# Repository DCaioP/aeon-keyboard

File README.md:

# Documentação do Sistema

## Sumário
- [Dados do Cliente](#dados-do-cliente)
- [Equipe de Desenvolvimento](#equipe-de-desenvolvimento)
- [Introdução](#introdução)
- [Objetivo](#objetivo)
- [Escopo](#escopo)
- [Backlogs do Produto](#backlogs-do-produto)
- [Cronograma](#cronograma)
- [Materiais e Métodos](#materiais-e-métodos)
- [Resultados](#resultados)
- [Conclusão](#conclusão)
- [Homologação do MVP junto ao Cliente](#homologação-do-mvp-junto-ao-cliente)
- [Divulgação](#divulgação)
- [Carta de Apresentação](#carta-de-apresentação)
- [Carta de Autorização](#carta-de-autorização)
- [Relato Individual do Processo](#relato-individual-do-processo)

---

## Dados do Cliente

- **Título do Projeto**: aeon: Teclado Ergonômico Split Ortolinear
- **Cliente**: BrainX
- **CNPJ/CPF**: 58.450.889/0001-99
- **Contato**: Caio Pontes Magalhães
- **Email do contato**: caio@brainx.dev

---

## Equipe de Desenvolvimento

| Nome completo        | Curso                  | Disciplina                           |
|----------------------|------------------------|--------------------------------------|
| Caio Pontes Magalhães | Ciências da Computação | Programação de Software Básico em C  |
| <integrante 2>       | Ciências da Computação | Programação de Software Básico em C  |
| <integrante 3>       | Ciências da Computação | Programação de Software Básico em C  |
| <integrante 4>       | Ciências da Computação | Programação de Software Básico em C  |
| <integrante 5>       | Ciências da Computação | Programação de Software Básico em C  |

### Professor Orientador
<nome completo do professor>

---

## Introdução

<Uma introdução ao projeto deve constar o problema constatado pelo cliente. Em seguida, deve ser relatado, resumidamente, como serão resolvidos. Comente sobre as tecnologias que serão utilizadas para resolver o problema e por fim, em apenas uma frase, descreva também como seu sistema vai modificar (impacto causado) no processo do cliente. Este texto pode ser usado no forms de inscrição no CPEI/JUPESQI>

---

## Objetivo

<Qual problema que o cliente enfrenta, o qual será resolvido através de um sistema computadorizado? Por exemplo, “Automatizar o atendimento de balcão para que os pedidos sejam emitidos de forma automática para a cozinha do restaurante.>

---

## Escopo

<Escopo é o que será implementado no sistema. Coloque aqui os requisitos principais que serão implementados e até que ponto serão implementados, ou seja, quais os limites de implementação. Os requisitos citados aqui devem ser macros, ou seja, 2 ou 3 requisitos principais. Também é bom citar o que não será implementado.>

---

## Backlogs do Produto

<Neste capítulo, teremos uma lista expandida do Escopo. Liste aqui os Requisitos levantados junto ao cliente e pela equipe de desenvolvimento. Os requisitos devem ter uma breve explicação do que se trata. Caso já tenha feito isso no Jira, basta copiar para cá.>

- <Requisito 1>: <descrição>
- <Requisito 2>: <descrição>
- <Requisito 3>: <descrição>

---

## Cronograma

<Insira aqui uma imagem ou tabela de todo o planejamento do projeto (com atividades e datas). A periodicidade das tarefas será de 2 semanas. O cronograma deve abranger todo o processo de construção do projeto. Isso pode ser feito diretamente neste doc, no excel, canva etc>

---

## Materiais e Métodos

### Modelagem do Sistema
<A modelagem do seu sistema são diagramas (desenhos) da sua estrutura ou comportamento. A UML (Unified Modelling Language) oferece diversos diagramas para que você possa modelar seu sistema. Escolha, pelo menos, dois modelos e insira aqui. Por exemplo, Modelo de Dados (Diagrama de Classe ou MER), Casos de Uso, Diagrama de Sequência, Diagrama de Atividades etc.>

### Tecnologias Utilizadas
<Escreva quais linguagens foram utilizadas, quais frameworks, bibliotecas e API’s consumidas/criadas. Quais ferramentas foram usadas para desenho dos modelos. Para cada um deles, faça uma pequena descrição de uso.>

- <Tecnologia 1>: <descrição>
- <Tecnologia 2>: <descrição>

### Arquitetura do Sistema
<Insira aqui uma imagem contendo a arquitetura do sistema e o fluxo das informações. Se a arquitetura for muito simples, detalhe o fluxo dos processos.>

---

## Resultados

### Protótipo
<São as telas do software e suas descrições. Em cada uma delas, descreva as ações possíveis do usuário e reações do sistema. Isto pode ser feito através do print das telas do seu sistema.>

### Códigos das Principais Funcionalidades
<Copy-cole aqui as seções mais relevantes do seu código. Insira comentários sobre cada seção.>

```<linguagem>
<seção de código com comentários>
```

---

## Conclusão

### Impacto do Sistema
<Como o sistema impactou (alterou positivamente) o processo do cliente>

### Melhorias Futuras
<Elencar, pelo menos, uma melhoria que poderá ser realizada futuramente no sistema.>

---

## Homologação do MVP junto ao Cliente

Após as entregas parciais, realizadas de acordo com os requisitos do sistema e cronograma, o MVP foi apresentado em uma reunião, realizada entre o time de desenvolvedores e o cliente.

| <foto 1: foto do time e cliente com o primeiro slide de fundo> | <foto 2: foto de um integrante apresentando o MVP> |
|----------------------------------------------------------------|----------------------------------------------------|
| Da esquerda para direita: <legenda 1: descreva quem está na foto> | <legenda 2: coloque o nome de quem está apresentando> |
| <foto 3: foto dos participantes assistindo a homologação>     | <foto 4: foto do plano geral do local>            |
| Participantes da homologação assistindo a apresentação        | Participantes da homologação                      |

### Lista de Presentes na Homologação
<Cole aqui a foto da lista de presentes na homologação.>

Ao final da apresentação, o sistema foi homologado pelo cliente.

---

## Divulgação

### LinkedIn do Projeto
<A página do LinkedIn do projeto deve ter o logo do LTD, o título do projeto, um breve resumo, o nome dos integrantes e o nome do professor-orientador. Insira também o link do repositório do projeto no GitHub.>

| <print da tela de perfil do LinkedIn> | <link da pág do LinkedIn> |
|---------------------------------------|---------------------------|

### Seminário de Projetos de Software

#### Vídeo da Apresentação
<Grave sua apresentação, poste no LinkedIn do projeto e insira aqui o link público (acesso sem login) do vídeo da apresentação>

| <foto 1: foto do time com o primeiro slide de fundo> | <foto 2: foto de um integrante apresentando o sistema> |
|-------------------------------------------------------|--------------------------------------------------------|
| Da esquerda para direita: <legenda 1: descreva quem está na foto> | <legenda 2: coloque o nome de quem está apresentando> |
| <foto 3: foto plano geral da apresentação de frente para o fundo da sala> | <foto 4: foto plano geral da apresentação do fundo para a frente da sala> |
| Participantes do evento assistindo a apresentação                        | Participantes do evento assistindo a apresentação                        |

#### Lista de Presentes na Apresentação
<Faça uma lista de presença numa folha A4, contendo no alto da folha “Seminários de Projetos de Software”. A lista deve conter RA, nome e assinatura dos presentes. Cole aqui a foto desta lista.>

### FENETEC: Feira de Negócios em Tecnologia

#### Apresentação do Projeto
<Um vídeo deve ser produzido mostrando o time apresentando seu projeto para algum visitante. Insira aqui o link público deste vídeo.>

| <foto 1: foto do time ao lado do poster> | <foto 2: foto de um integrante apresentando o sistema> |
|-------------------------------------------|--------------------------------------------------------|
| Da esquerda para direita: <legenda 1: descreva quem está na foto> | <legenda 2: coloque o nome de quem está apresentando> |
| <foto 3: foto do público assistindo sua apresentação> | <foto 4: foto plano geral da FENETEC> |
| Participantes do evento assistindo a apresentação            | Estandes da FENETEC                          |

#### Lista de Presentes na Apresentação
<Cole aqui a lista de presença dos visitantes da FENETEC com nome e email do visitante.>

---

## Carta de Apresentação

Vimos por desta apresentar o grupo de acadêmicos do Centro Universitário Unimetrocamp, localizada à Rua Sales de Oliveira, 1661 - Campinas - SP, a fim de convidá-lo a participar de uma atividade extensionista associada ao componente curricular <inserir o nome da disciplina>, sob responsabilidade do orientador Prof. Kesede Rodrigues Julio (profkesede64@gmail.com).

Em consonância ao Plano Nacional de Educação vigente, o Centro Universitário Unimetrocamp promove o Desenvolvimento de Software que, norteados pela metodologia de Gerenciamento Ágil Scrum, tem por princípios fundantes o diagnóstico dos problemas/demandas/necessidades, a participação ativa dos interessados/públicos participantes, a construção dialógica, coletiva e experiencial de conhecimentos, o planejamento de ações, o desenvolvimento e avaliação das ações, a sistematização dos conhecimentos, a avaliação das ações desenvolvidas.

Nesse contexto, a disciplina acima mencionada tem como principal escopo os temas relacionados à Programação Orientada à Objeto / Padrões de Projetos de Software, no que diz respeito ao desenvolvimento de um software utilizando Programação Orientada à Objeto.

Sendo assim, pedimos o apoio de <nome do cliente> para a realização das seguintes atividades: levantamento de requisitos, validação das entregas parciais, revalidação dos requisitos, homologação do MVP, ou qualquer outra intervenção que auxilie no desenvolvimento das competências de nossos acadêmicos e ao mesmo tempo possa contribuir para a comunidade em que estamos inseridos.

Aproveitamos a oportunidade para solicitarmos, em caso de aceite, que a parceria seja formalizada, mediante assinatura da Carta de Autorização, as atividades e informações que o(s) aluno(s) poderá(ão) ter acesso.

Em tempo, registramos ainda, o convite para a participação de todos os interessados no fórum semestral de acompanhamento e avaliação das atividades realizadas, que está previsto para o final deste semestre, e será comunicado previamente em convite específico.

Desde já nos colocamos à sua disposição para quaisquer esclarecimentos.

Atenciosamente,  
Campinas, ____ de _________ de 202___.  

_____________________________  
Assinatura Direção Acadêmica da IES  

_____________________________  
Assinatura Docente  

---

## Carta de Autorização

Eu, (preencher com nome do responsável), (preencher com cargo ocupado), da (nome da empresa, organização, associação, escola, secretaria, etc., situada no endereço – inserir o endereço), autorizo a realização das seguintes atividades acadêmicas do componente extensionista <código e nome da disciplina>, do Centro Universitário Unimetrocamp, sob orientação do Prof. Kesede Rodrigues Julio.

### Atividades:
- <Atividade 1>
- <Atividade 2>

Conforme combinado em contato prévio, as atividades acima descritas são autorizadas para os seguintes alunos:

| Nome dos/das alunos/as | Curso | Matrícula |
|-------------------------|-------|-----------|
|                        |       |           |
|                        |       |           |
|                        |       |           |
|                        |       |           |
|                        |       |           |

Declaro que fui informado por meio da Carta de Apresentação sobre as características e objetivos das atividades que serão realizadas na organização/instituição/empresa a qual represento e afirmo estar ciente de tratar-se de uma atividade realizada com intuito exclusivo de ensino de alunos de graduação, sem a finalidade de exercício profissional.

Desta forma, autorizo, em caráter de confidencialidade:
- [ ] O acesso a informações e dados que forem necessários à execução da atividade;
- [ ] O registro de imagem por meio de fotografias;
- [ ] Outro: (especificar)

Campinas, ___ de ___________ de 202_.  

___________________________________________________________________  
(Assinatura, nome completo do responsável, email de contato e com carimbo da empresa)

---

## Relato Individual do Processo

### <nome do aluno>
<Um breve relato pessoal sobre o trabalho extensionista desenvolvido>

### <nome do aluno>
<Um breve relato pessoal sobre o trabalho extensionista desenvolvido>

### <nome do aluno>
<Um breve relato pessoal sobre o trabalho extensionista desenvolvido>

### <nome do aluno>
<Um breve relato pessoal sobre o trabalho extensionista desenvolvido>

### <nome do aluno>
<Um breve relato pessoal sobre o trabalho extensionista desenvolvido>

---

Esse documento agora está em formato Markdown e pode ser usado como um README em um repositório GitHub. Para compartilhar com o orientador, você pode salvá-lo como `README.md`, fazer o upload no GitHub como "raw" e enviar o link para `profkesede64@gmail.com`. Certifique-se de preencher os campos placeholders (<...>) conforme o progresso do projeto e as instruções do arquivo “CALENDÁRIO DE PROJETOS.2025.1”.

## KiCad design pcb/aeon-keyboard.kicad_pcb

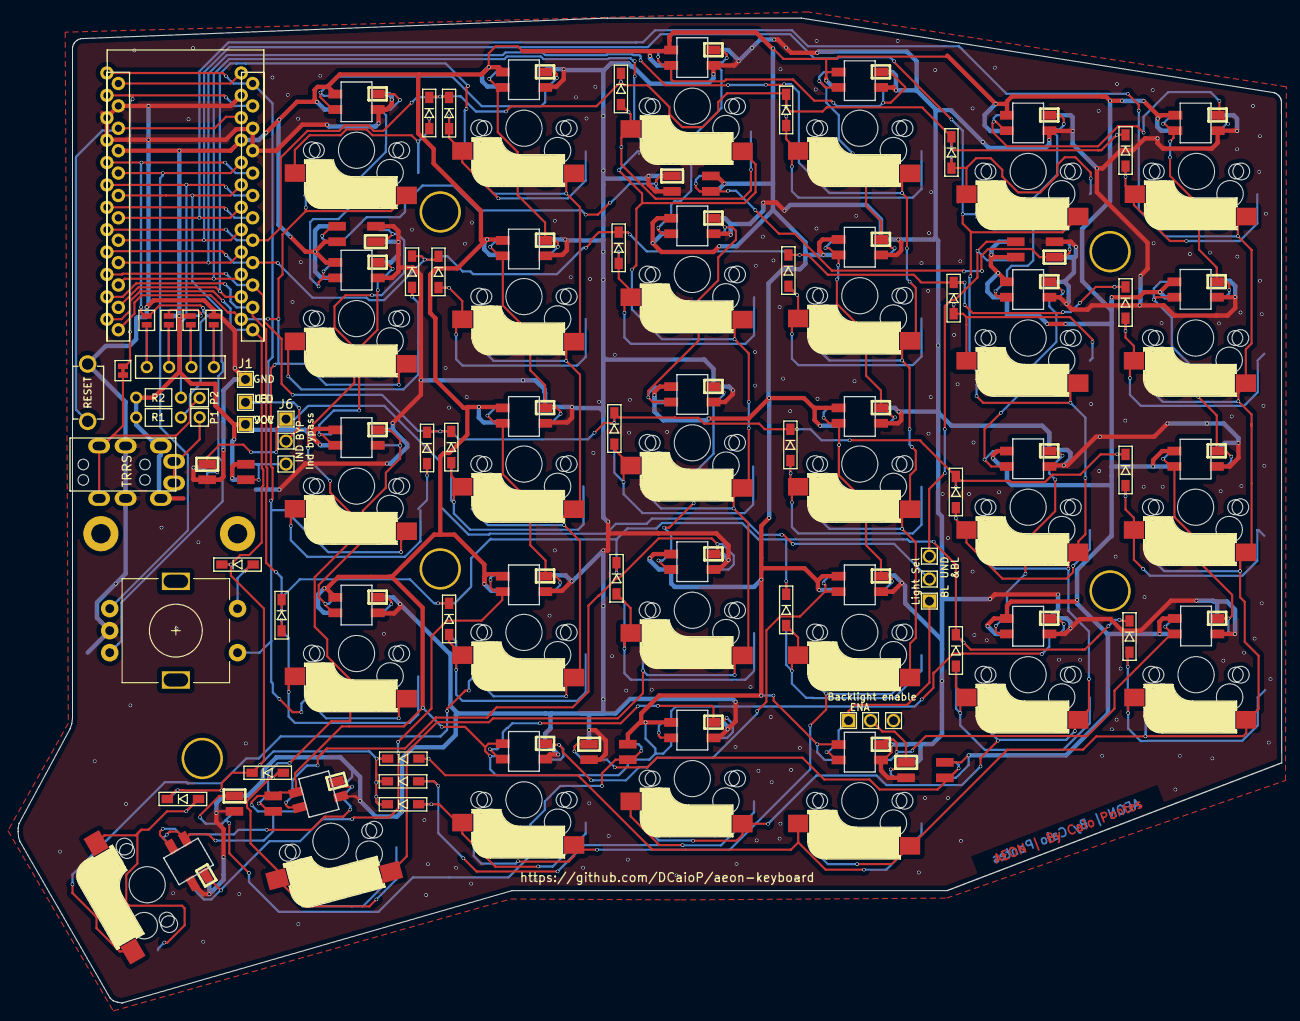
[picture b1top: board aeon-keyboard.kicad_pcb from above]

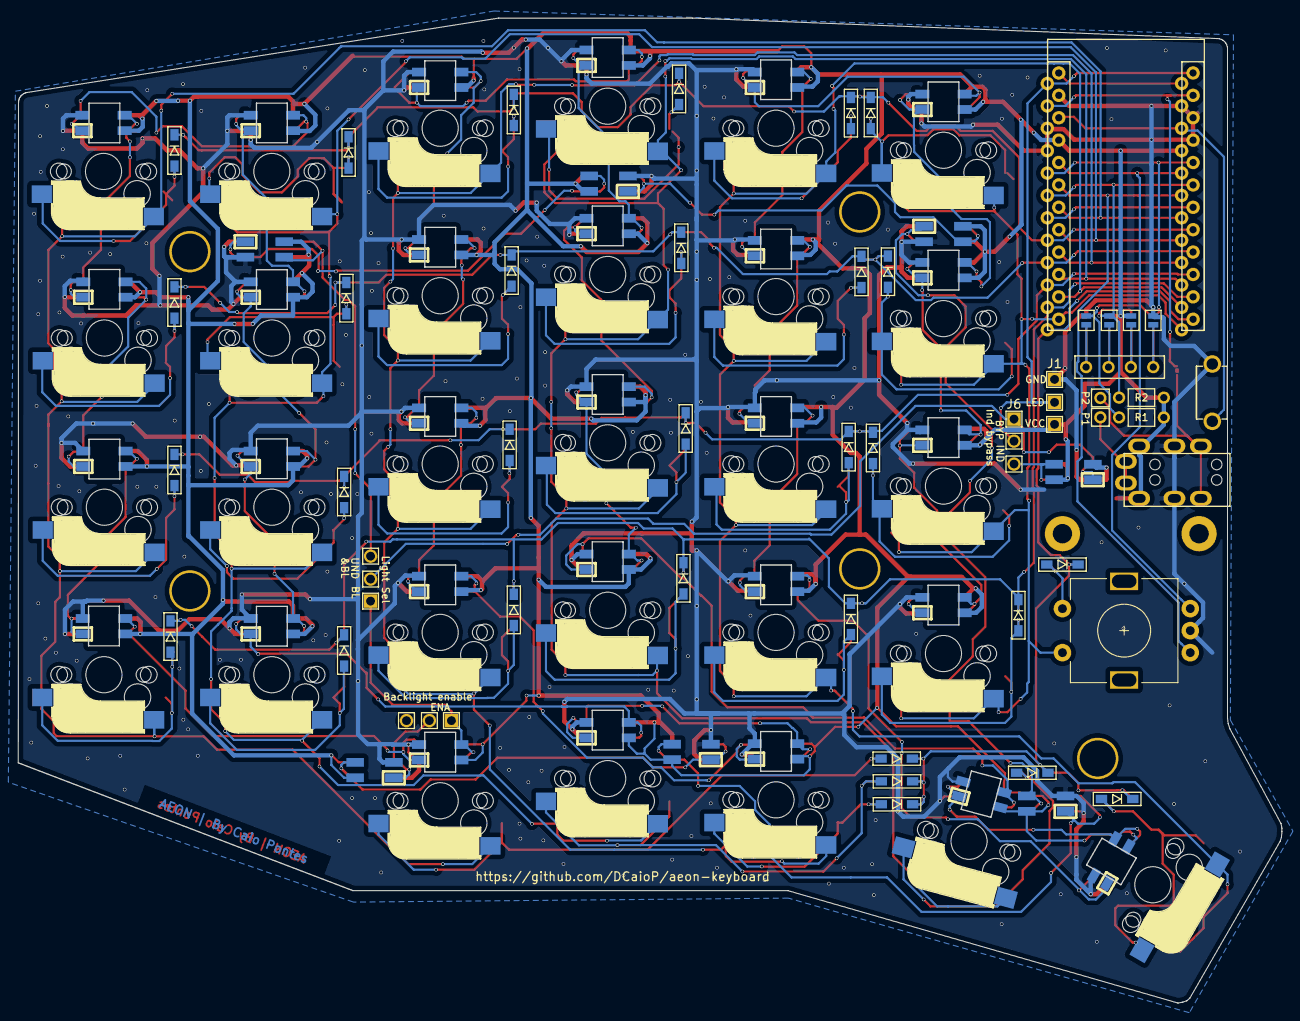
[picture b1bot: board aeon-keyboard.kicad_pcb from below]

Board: 6 copper layers, 143.4 x 111.8 mm, 95 parts (4 on the bottom side), 94 nets.

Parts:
D1, D2, D3, D4, D5, D6, D7, D8, D9, D10, D11, D12, D13, D14, D15, D16, D17, D18, D19, D20, D21, D22, D23, D24, D25, D26, D27, D28, D29, D30: D; crkbd-diode
D31, D32, D33, D34, D35, D36, D37: LED_sk2812_SM; SK6812MINI_underglow_dev
J1: LED
J2: 4PIN; MJ-4PP-9
J3: OLED; OLED_4Pin
J4: key leds; 3x1header
J5: backlight sel; 3x1header
J6: indicator bypass; 3x1header
JP1, JP2, JP3, JP4, JP5, JP6, JP7, JP8: Jumper_NO_Small; Jumper
P1, P2: i2c_pin; 1pin_conn
R1, R2: R; RESISTOR_mini
RSW1: SW_RST; TACT_SWITCH_TVBP06
SW1, SW2, SW3, SW4, SW5, SW6, SW7, SW8, SW9, SW10, SW11, SW12, SW13, SW14, SW15, SW16, SW17, SW18, SW19, SW20, SW21, SW22, SW23, SW24, SW26, SW27, SW28, SW29, SW30: SW_PUSH-MX_W_LED; SK6812MINI_and_cherry
SW25: Rotary_Encoder_Switch; RotaryEncoder_Alps_EC11E-Switch_Vertical_H20mm-keebio_modif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
TH1, TH2: HOLE; M2_HOLE_PCB
TH3, TH4, TH5, TH6, TH7: HOLE; HOLE_M2_TH
U1: ProMicro
W1: jumper; jumper_data

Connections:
/backlight: J4.1, J5.1, SW30.3
/i2c_c: J2.4, P1.1
/i2c_d: J2.3, P2.1, W1.2
/underglow: D33.3, J4.3
DATA: U1.2, W1.1
ENCA: SW25.A, U1.20
ENCB: SW25.B, U1.19
GND: D31.2, D32.2, D33.2, D34.2, D35.2, D36.2, D37.2, J1.3, J2.2, JP1.2, JP8.2, RSW1.1, SW1.2, SW2.2, SW3.2, SW4.2, SW5.2, SW6.2, SW7.2, SW8.2, SW9.2, SW10.2, SW11.2, SW12.2, SW13.2, SW14.2, SW15.2, SW16.2, SW17.2, SW18.2, SW19.2, SW20.2, SW21.2, SW22.2, SW23.2, SW24.2, SW25.C, SW26.2, SW27.2, SW28.2, SW29.2, SW30.2, U1.3, U1.4, U1.23
LED: J1.2, J6.2, U1.1
unnamed: D1.2, SW1.5
unnamed: D2.2, SW2.5
unnamed: D3.2, SW3.5
unnamed: D4.2, SW4.5
unnamed: D5.2, SW5.5
unnamed: D6.2, SW6.5
unnamed: D7.2, SW7.5
unnamed: D8.2, SW8.5
unnamed: D9.2, SW9.5
unnamed: D10.2, SW10.5
unnamed: D11.2, SW11.5
unnamed: D12.2, SW12.5
unnamed: D13.2, SW13.5
unnamed: D14.2, SW14.5
unnamed: D15.2, SW15.5
unnamed: D16.2, SW16.5
unnamed: D17.2, SW17.5
unnamed: D18.2, SW18.5
unnamed: D19.2, SW19.5
unnamed: D20.2, SW20.5
unnamed: D21.2, SW21.5
unnamed: D22.2, SW22.5
unnamed: D23.2, SW23.5
unnamed: D24.2, SW24.5
unnamed: D26.2, SW26.5
unnamed: D27.2, SW27.5
unnamed: D28.2, SW28.5
unnamed: D29.2, SW29.5
unnamed: D30.2, SW30.5
unnamed: D31.1, D34.3
unnamed: D31.3, D32.1
unnamed: D32.3, D33.1
unnamed: D34.1, D35.3
unnamed: D35.1, D36.3
unnamed: D36.1, J5.2
unnamed: D37.3, J6.3
unnamed: J3.1, JP4.1, JP8.1
unnamed: J3.2, JP3.1, JP7.1
unnamed: J3.3, JP2.1, JP6.1
unnamed: J3.4, JP1.1, JP5.1
unnamed: SW1.1, SW7.3
unnamed: SW1.3, SW2.1
unnamed: SW2.3, SW8.1
unnamed: SW3.1, SW9.3
unnamed: SW3.3, SW4.1
unnamed: SW5.3, SW6.1
unnamed: SW4.3, SW10.1
unnamed: SW10.3, SW16.1
unnamed: SW11.1, SW17.3
unnamed: SW5.1, SW11.3
unnamed: SW6.3, SW12.1
unnamed: SW12.3, SW18.1
unnamed: SW13.1, SW19.3
unnamed: SW7.1, SW13.3
unnamed: SW8.3, SW14.1
unnamed: SW14.3, SW20.1
unnamed: SW15.1, SW21.3
unnamed: SW9.1, SW15.3
unnamed: SW16.3, SW22.1
unnamed: SW17.1, SW23.3
unnamed: SW18.3, SW24.1
unnamed: SW20.3, SW26.1
unnamed: SW21.1, SW27.3
unnamed: SW22.3, SW28.1
unnamed: SW23.1, SW29.3
unnamed: SW24.3, SW30.1
unnamed: SW26.3, SW27.1
unnamed: SW28.3, SW29.1
RESET: RSW1.2, U1.22
SCL: JP3.2, JP6.2, R2.2, U1.6
SDA: JP4.2, JP5.2, R1.2, U1.5
SW25A: SW1.6, SW7.6, SW13.6, SW19.6, SW25.S1, U1.13
SW25B: D25.2, SW25.S2
VCC: D31.4, D32.4, D33.4, D34.4, D35.4, D36.4, D37.4, J1.1, J2.1, JP2.2, JP7.2, R1.1, R2.1, SW1.4, SW2.4, SW3.4, SW4.4, SW5.4, SW6.4, SW7.4, SW8.4, SW9.4, SW10.4, SW11.4, SW12.4, SW13.4, SW14.4, SW15.4, SW16.4, SW17.4, SW18.4, SW19.4, SW20.4, SW21.4, SW22.4, SW23.4, SW24.4, SW26.4, SW27.4, SW28.4, SW29.4, SW30.4, U1.21
col0: SW6.6, SW12.6, SW18.6, SW24.6, SW30.6, U1.18
col1: SW5.6, SW11.6, SW17.6, SW23.6, SW29.6, U1.17
col2: SW4.6, SW10.6, SW16.6, SW22.6, SW28.6, U1.16
col3: SW3.6, SW9.6, SW15.6, SW21.6, SW27.6, U1.15
col4: SW2.6, SW8.6, SW14.6, SW20.6, SW26.6, U1.14
lights: D37.1, J4.2, J6.1
row0: D1.1, D2.1, D3.1, D4.1, D5.1, D6.1, U1.8
row1: D7.1, D8.1, D9.1, D10.1, D11.1, D12.1, U1.9
row2: D13.1, D14.1, D15.1, D16.1, D17.1, D18.1, U1.10
row3: D19.1, D20.1, D21.1, D22.1, D23.1, D24.1, U1.11
row4: D25.1, D26.1, D27.1, D28.1, D29.1, D30.1, U1.12

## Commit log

2025-03-18 trash
